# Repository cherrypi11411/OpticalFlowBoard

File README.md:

# OpticalFlowBoard
Hardware design and source code for OpticalFlowBoard

We are [Team 11411 Cherry Pi](https://cherrypi.egoslike.us/). We are a FIRST Tech Challenge (FTC) robotics team based in San Diego, California. Over the past several years, one of the biggest challenges we see with the robots is how to determine where the robot is accurately. During our journey, we discovered many ways to approach this problem. One that looked especially promising is using an optical flow sensor similar to what is available for many optical mice. One such product is produced by PixArt, the [PMW-3901 chip](http://www.pixart.com.tw/product_data.asp?product_id=168&productclassify_id=19&productclassify2_id=&productclassify_name=&productclassify2_name=&partnumber=PMW3901MB-TXQT).

This chip is especially attractive as it is designed for robotics/drone usage with the sensor at a distance from the surface. Many mice sensors require a very close distance to surfaces to operate properly. A big disadvantage of this chip for our purposes is that it uses SPI for communication. Within FTC, SPI is not an option for sensor integration. Instead, analog, digital or I2C sensors are allowed.

We then experimented with translating SPI to I2C and created a prototype using these two products:
* The [Butterfly Board](https://www.tindie.com/products/TleraCorp/butterfly-stm32l433-development-board/)
* The [PMW-3901 Sensor Board](https://www.tindie.com/products/onehorse/pmw3901-optical-flow-sensor/)

These products are open source designs so inspired by those designs, some of our students created a new design combining the two boards together into a unified product. We then investigated getting the boards manufactured and eventually got in contact with [Advanced Assembly](http://www.aapcb.com/). When we described our project to them and that this board was being designed and programmed by middle and high school age kids, they were excited to help us out and graciously provided feedback on our design as well as offering to manufacture an initial run of boards for prototyping for free to us.

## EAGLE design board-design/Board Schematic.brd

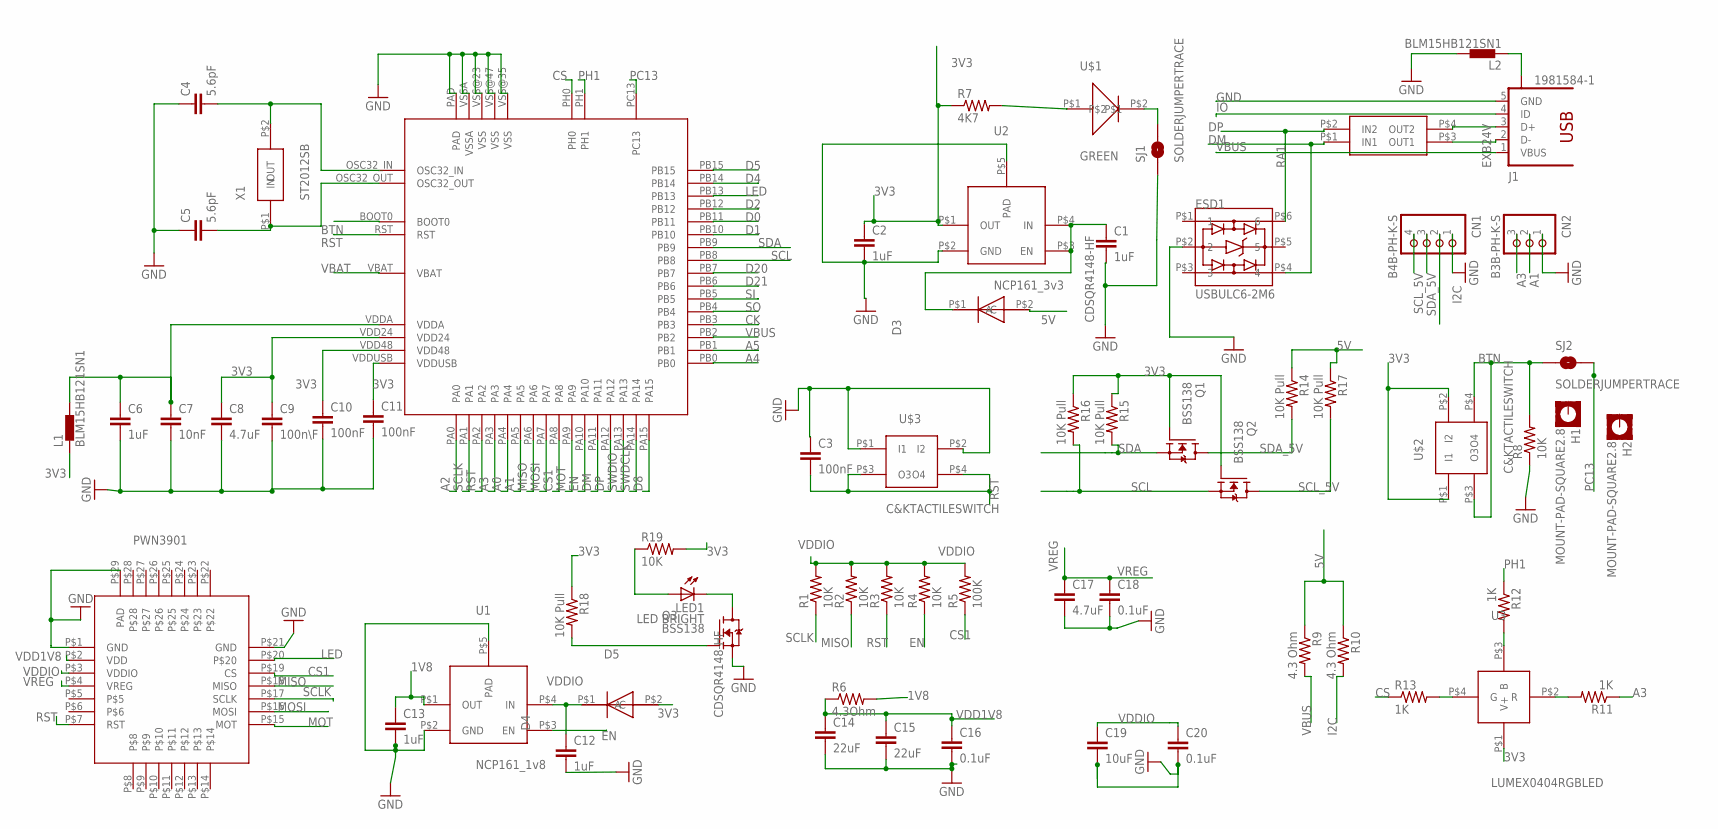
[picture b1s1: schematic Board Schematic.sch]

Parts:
C1, C2, C6, C12, C13: 1uF; 0402-CAP
C3, C10, C11: 100nF; 0402-CAP
C4, C5: 5.6pF; 0402-CAP
C7: 10nF; 0402-CAP
C8, C17: 4.7uF; 0402-CAP
C9: 100n\F; 0402-CAP
C14, C15: 22uF; 0402-CAP
C16, C18, C20: 0.1uF; 0402-CAP
C19: 10uF; 0402-CAP
CN1: B4B-PH-K-S
CN2: B3B-PH-K-S
D3, D4: CDSQR4148-HF
ESD1: USBULC6-2M6; UQFN6
H1, H2: MOUNT-PAD-SQUARE2.8; 2,8-PAD-SQUARE
J1: 1981584-1
L1, L2: BLM15HB121SN1; 0402
LED1: LED BRIGHT; LM561C
PWN3901: COB_PMW3901; COB
Q1, Q2, Q3: BSS138; SOT23
R1, R2, R3, R4, R8, R19: 10K; 0402-RES
R5: 100K; 0402-RES
R6: 4.3Ohm; 0402-RES
R7: 4K7; 0402-RES
R9, R10: 4.3 Ohm; 0402-RES
R11, R12, R13: 1K; 0402-RES
R14, R15, R16, R17, R18: 10K Pull; 0402-RES
RA1: EXB24V
SJ1, SJ2: SOLDERJUMPERTRACE; SJ_2S-TRACE
U1: NCP161_1v8; NCP161
U2: NCP161_3v3; NCP161
U3: LUMEX0404RGBLED; LX0404
U$1: GREEN; 0402LED
U$2, U$3: C&KTACTILESWITCH
U$4: STM32L433; QFN50P700X700X60-49N
X1: ST2012SB

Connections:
1V8: C13.1, R6.2, U1.P$1 (OUT)
3V3: C2.1, C8.1, C9.1, C10.1, C11.1, D4.P$2 (A), L1.1, Q1.1 (G), Q2.1 (G), R7.1, R15.1, R16.1, R18.1, R19.2, U2.P$1 (OUT), U3.P$1 (V+), U$2.P$1 (I1), U$2.P$2 (I2), U$4.VDD24, U$4.VDD48, U$4.VDDUSB
5V: D3.P$2 (A), R9.1, R10.1, R14.1, R17.1
A0: U$4.PA4
A1: CN2.2, U$4.PA5
A2: U$4.PA0
A3: CN2.3, R11.1, U$4.PA3
A4: U$4.PB0
A5: U$4.PB1
BTN: R8.2, SJ2.1, U$2.P$3 (O3), U$2.P$4 (O4), U$4.BOOT0
CK: U$4.PB3
CS: R13.1, U$4.PH0
CS1: PWN3901.P$19 (CS), R5.1, U$4.PA8
D0: U$4.PB11
D1: U$4.PB10
D2: U$4.PB12
D4: U$4.PB14
D5: Q3.1 (G), R18.2, U$4.PB15
D8: U$4.PA15
D20: U$4.PB7
D21: U$4.PB6
DM: ESD1.P$4 (4), RA1.P$1 (IN1), U$4.PA11
DP: ESD1.P$6 (6), RA1.P$2 (IN2), U$4.PA12
EN: R4.1, U1.P$3 (EN), U$4.PA10
GND: C1.2, C2.2, C3.1, C4.1, C5.1, C6.2, C7.2, C8.2, C9.2, C10.2, C11.2, C12.2, C13.2, C14.2, C15.2, C16.2, C17.2, C18.2, C19.2, C20.2, CN1.1, CN2.1, ESD1.P$2 (2), J1.5 (GND), L2.2, PWN3901.P$1 (GND), PWN3901.P$21 (GND), PWN3901.P$29 (PAD), Q3.2 (S), R8.1, SJ1.1, U1.P$2 (GND), U1.P$5 (PAD), U2.P$2 (GND), U2.P$5 (PAD), U$3.P$1 (I1), U$3.P$2 (I2), U$4.PAD, U$4.VSS@23 (VSS), U$4.VSS@35 (VSS), U$4.VSS@47 (VSS), U$4.VSSA
I2C: CN1.2, R10.2
IO: J1.4 (ID)
LED: PWN3901.P$20, U$4.PB13
MISO: PWN3901.P$18 (MISO), R2.1, U$4.PA6
MOSI: PWN3901.P$16 (MOSI), U$4.PA7
MOT: PWN3901.P$15 (MOT), U$4.PA9
unnamed: C4.2, U$4.OSC32_IN, X1.P$2 (OUT)
unnamed: C6.1, C7.1, L1.2, U$4.VDDA
unnamed: R13.2, U3.P$4 (G)
unnamed: C5.2, U$4.OSC32_OUT, X1.P$1 (IN)
unnamed: R12.2, U3.P$3 (B)
unnamed: R11.2, U3.P$2 (R)
unnamed: J1.S1, L2.1
unnamed: J1.3 (D+), RA1.P$4 (OUT2)
unnamed: J1.2 (D-), RA1.P$3 (OUT1)
unnamed: R7.2, U$1.P$1
unnamed: SJ1.2, U$1.P$2
unnamed: LED1.A1 (A), LED1.A2 (A), LED1.A3 (A), R19.1
unnamed: LED1.C1 (C), LED1.C2 (C), LED1.C3 (C), Q3.3 (D)
unnamed: C1.1, D3.P$1 (C), U2.P$3 (EN), U2.P$4 (IN)
PC13: SJ2.2, U$4.PC13
PH1: R12.1, U$4.PH1
RST: C3.2, PWN3901.P$7 (RST), R3.1, U$3.P$3 (O3), U$3.P$4 (O4), U$4.PA2, U$4.RST
SCL: Q2.2 (S), R16.2, U$4.PB8
SCLK: PWN3901.P$17 (SCLK), R1.1, U$4.PA1
SCL_5V: CN1.4, Q2.3 (D), R17.2
SDA: Q1.2 (S), R15.2, U$4.PB9
SDA_5V: CN1.3, Q1.3 (D), R14.2
SI: U$4.PB5
SO: U$4.PB4
SWDCLK: U$4.PA14
SWDIO: U$4.PA13
VBAT: U$4.VBAT
VBUS: J1.1 (VBUS), R9.2, U$4.PB2
VDD1V8: C14.1, C15.1, C16.1, PWN3901.P$2 (VDD), R6.1
VDDIO: C12.1, C19.1, C20.1, D4.P$1 (C), PWN3901.P$3 (VDDIO), R1.2, R2.2, R3.2, R4.2, R5.2, U1.P$4 (IN)
VREG: C17.1, C18.1, PWN3901.P$4 (VREG)

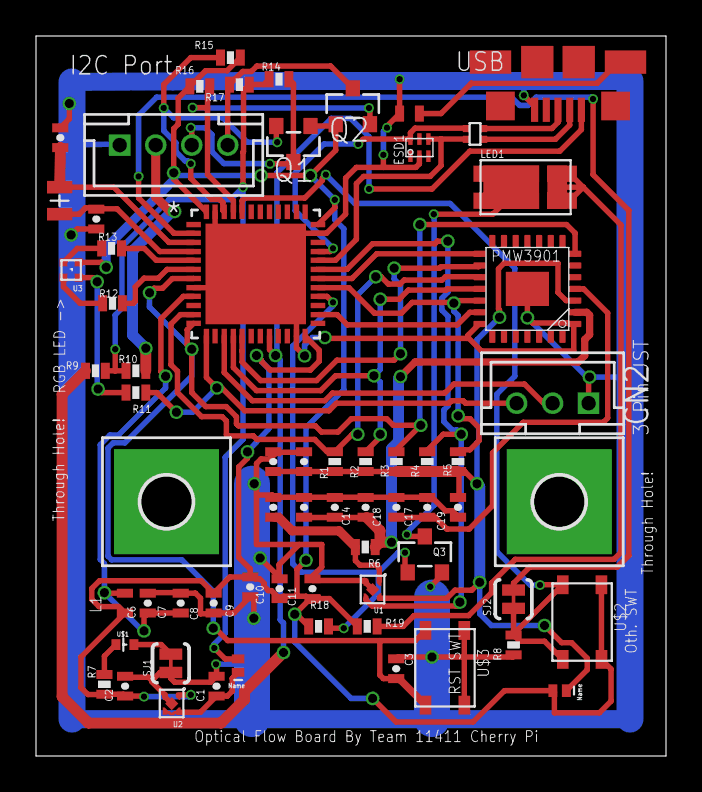
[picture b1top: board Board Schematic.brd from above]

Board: 2 copper layers, 35.0 x 40.0 mm, 65 parts (0 on the bottom side), 44 nets.

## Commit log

2018-12-27 Add board designs
2018-12-27 Code for microcontroller
2018-12-27 Initial FTC code
2018-12-27 Add some images
2018-12-27 Add some more images
2018-12-27 Remove unneeded imports

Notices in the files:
parts and their libraries:
SparkFun-Resistors: Licensing: Creative Commons ShareAlike 4.0 International - https://creativecommons.org/licenses/by-sa/4.0
